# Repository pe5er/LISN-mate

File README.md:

# LISN-mate
This design a fork of CompuPhase's "LISN mate", suitable for a dual channel LISN. 

The original design was published in Elektor [2021], and is
available from the ["elektorstore"](https://www.elektor.com/elektor-dual-dc-lisn-150-khz-200-mhz)
as a kit.

A LISN lets you test the conducted emissions in power cables. If the emissions
exceed the limit, and you need to adjust the design to reduce the RF noise, the
first thing you will want to know is whether the noise is primarily "common mode"
or "differential mode". The LISN-mate is a tool that tells you that.

There's nothing wrong with the original design, I just had some specific requirements in mind.

.png)

When you want a quantitative value for the common mode noise and/or the differential
mode noise (in dB&micro;V), a LISN-mate is actually somewhat complex circuit. 
However, there is just a single limit for conducted emissions in the EMC/EMI standards,
so you do not really need the absolute values. What you need to know, whether the emissions 
are *primarily* either common mode or differential mode. For a LISN-mate that gives you an
answer on that issue, all it takes is a transformer.

The design is in Altium. Gerber files for the PCB are provided as well. The components are:

| Number | Part number          | Manufacturer          | Description                             |
| ------ | -------------------- | --------------------- | --------------------------------------- |
|  1     | ADT1-6T              | Mini-Circuits         | RF Transformer 50 Ohm, 30 kHz - 125 MHz |
|  4     | 60312242114510       | Würth Elektronik      | SMA receptable, edge-mount              |
|  1     | 1457C802EBK          | Hammond Enclosures    | Enclosure, extrusion cut down to fit    |

The enclosure is not the correct length, so you must cut down the extrusion to fit!

## License

The LISN-mate is distributed under the CC BY-NC-SA 4.0 license (Attribution-NonCommercial-ShareAlike 4.0 International).

You are free to:

> **Share** —  copy and redistribute the material in any medium or format <br>
> **Adapt** — remix, transform, and build upon the material <br>
> The licensor cannot revoke these freedoms as long as you follow the license terms.

Under the following terms:

> **Attribution** - You must give appropriate credit, provide a link to the license, and indicate if changes were made. You may do so in any reasonable manner, but not in any way that suggests the licensor endorses you or your use.  <br>
> **NonCommercial** - You may not use the material for commercial purposes.  <br>
> **ShareAlike** - If you remix, transform, or build upon the material, you must distribute your contributions under the same license as the original. <br>
> **No additional restrictions** - You may not apply legal terms or technological measures that legally restrict others from doing anything the license permits.

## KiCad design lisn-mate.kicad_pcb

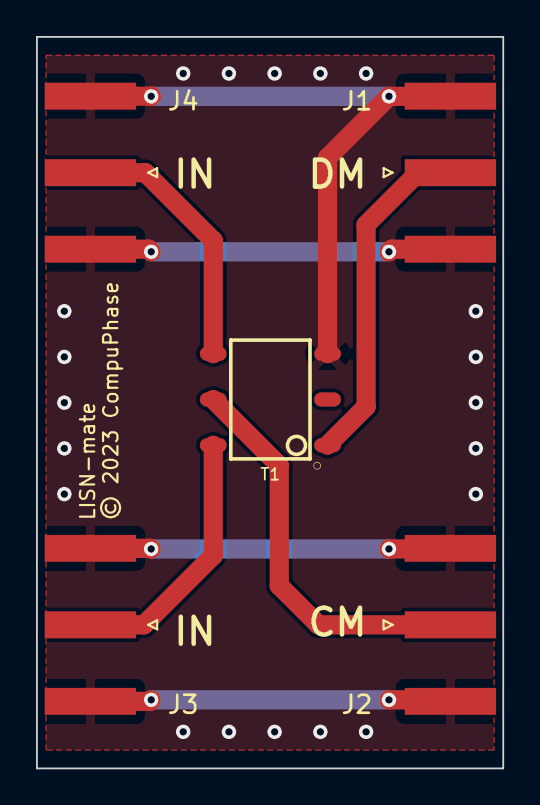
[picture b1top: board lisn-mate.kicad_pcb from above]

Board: 2 copper layers, 25.9 x 40.6 mm, 5 parts (0 on the bottom side), 5 nets.

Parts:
J1: DM; SMA_Amphenol_132289_EdgeMount
J2: CM; SMA_Amphenol_132289_EdgeMount
J3, J4: IN; SMA_Amphenol_132289_EdgeMount
T1: Transformer_1P_SS; SOP6

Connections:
GND: J1.2 (Ext), J2.2 (Ext), J3.2 (Ext), J4.2 (Ext), T1.3 (AB)
unnamed: J1.1 (In), T1.1 (AA)
unnamed: J2.1 (In), T1.5 (SC)
unnamed: J3.1 (In), T1.6 (SB)
unnamed: J4.1 (In), T1.4 (SA)

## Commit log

2023-09-29 Initial commit.
2023-09-29 Update README.md
    Formatting
2023-09-29 Update README.md
    Added pictures
2023-09-29 Added picture of shielded PCB.
2023-09-30 Adjustment of the height of the 3D printed case to adjust for the thickness of the copper shield.
2023-10-01 Update README.md
    Correction in license, added item to BOM.
2024-01-07 Update README.md
    Clarification of a somewhat ambiguous sentence.
2025-06-23 swapped to updated altium project

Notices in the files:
lisn-mate.kicad_pcb:
© 2023 CompuPhase
